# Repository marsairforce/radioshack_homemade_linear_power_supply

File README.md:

# Vintage Adjustable Linear Power Supply

Updating and improving on a very early project I built.

* Partly because I want something to do more things - dual tracking adjustable regulated outputs.
* Partly because I wanted to see how far I have come in my design skills from 10 year old me.
* Partly because I am bored

 I have been wanting to get more into analog circuits, like op-amp circuits and amplifiers. Building these on breadboards has always been challenging for me because I have always had only one bench power supply.  I have a modern bench power supply, but it also only has one output on it.

## TL;DR

This is now a dual channel, double trackking voltage power supply.

Each channel can do about +/-1.2V to +/-20V at about 1A

## Analysis

I created this (I think) when I was in grade 4. So probably around 1987?

* Simple 317 regulator based adjustable power supply.

* Most components were baught from local Radio Shack store in St Vital mall.

  * Radio Shack project box.
  * 18V CT, 2A (36VA?) transformer.
  * Bridge Rectifier.
  * 2200uF capacitor
  * 317 volt regulator on free hanging heatsink.
  * Basic power connector, switch, fuze, with shitty heat shrink tubing on it.
  * Analog DC volt meter.
  * Indicator lamp, but bulb burnt out so I replaced it at some time with a LED stuffed into the lamp holder.
  * A pointless inline fuse holder, with a 2A fuse. This never would blow because the thing can only source 1A
  * Adjustable voltage knob - I remember getting this multi turn potentiometer from Active Electronics.
  * Custom etched single sided PCB
  * Serrible banana plug jacks.
  * Board standoffs (Active Electronics - I still have these) with stove bolts from hardware store.

I would like to say "I have come a long way since then". But at the same time, not really.

* I don't have a convenient way to make circuit boards at home any more.

This gem was hand drawn with a sharpie and then using a liquid tin to protect the copper.

In hindsight this is a terrible board layout.

* I still do not have good nuts and bolts hardware to mount circuit boards.

I have learned or improved a little bit more since I built this:

* I do have much better selection of wires now.

* My soldering skills are a lot better. This thing looks like a Halloween house of horrors.

## Original Schematic

I created this in Kicad

This still functioned very well.

Funny notes as I was taking the old circuit apart.

* The C1 makes no sense. Why did I think I needed to have a ac line capacitor here? I probably had these and copied what I saw in other power supplies.
* The F1 should be after the switch on the hot side.
* The wires from J1, S1, T1 were a white lamp cord. I remember having this and using it for everything.
* The wires from T1 to the circuit board and everywhere else were from an old datacom cable I salvaged from one of my dad's construction sites. I stripped the cable jacket and used the wires for projects.
* I made a PCB using the kit from RadioShack. It is horrible layout and terrible pattern. But I did it with a sharpie and I was 8.
* The J2 was a metal not insulated binding post. As a kid I converted it into an insulated binding post by placing a piece of plastic drinking straw around the metal screw part of the  between the connector and the chassis. Somehow it continued to work all these years.

## Improvements

As usual I can't leave anything alone. Nothing is ever truly completed is it.

I ripped apart the old circuit and removed the parts from the chassis.  The front panel and bottom was a bit bent up from this being knocked around in storage I guess.

### Support more current output

* [Researching](https://www.homemade-circuits.com/lm317-with-outboard-current-boost/) adding a transistor to boost the current handling.

* https://www.ti.com/lit/ds/slvs044x/slvs044x.pdf

This is fun. But I think this is too complicated. And the parts and heatsinks will take up too much space in this small chassis.

And considering the power transformer here is very small, I would be able to fully use this.

Instead, let's just use a [LD1085D2T-R‎](https://www.digikey.ca/product-detail/en/LD1085D2T-R/497-3424-1-ND/669200/?itemSeq=339103460). This has a power capacity of 3A.  And being a surface mount device I can use the PCB as the heatsink.

## More voltage outputs

I think having a single output is kind of useless for me.

* To build a variable output. But to build it as a [dual tracking control](https://www.youtube.com/watch?v=AOIxS7iOxbU). This is pretty neat. But the devil in the details of the op-amp needs a +/- power supply.

* A +/-15V supply for op-amps.

> HEY!!  I had "build a nice bench top op-amp power supply as one of my active projects.  I never got it out of design phase though. But what if I just build it into this existing power supply chassis I alredy have.  That seems practical to me too.

The dual tracking adjustable supply is neat as I do not have this with my existing bench top power supplies.

I think it is going to be challenging to fit all this stuff into this small chassis.

I compromised and designed a dual output dual tracking power supply. This gives me two channels of adjustable +/- voltage.

Each channel allows the use of a trimmer pot on the pcb, so it can practically behave as a fixed voltage.

I think I will go with having one channel be variable from the front panel and the other to be set with a trimmer.

## Updated schematic

This is in the updated folder, opamp_power_supply sub folder.

I started off with this Hammoond 229B34. It is a nice 12VA low profile transformer. It is semi-toroidial, so it has ok magnetic shielding as well. I was looking for something that had low electrical and magnetic noise. The original idea was to create a power supply suitable for powering audio op-amp circuits.

The configuration of this transformer lends itself to being able to use the secondary in series or in parallel.  In this case the secondary series voltage was about 38V. I don't need a power supply to go that high, so most of the voltage would be disapated as heat.
using the transformer secondary in parallel gives about 18V and about 600ma current output. But then is only single supply.
The approach here where I use them as separate secondaries is somewhere in between. I have an ok voltage to supply the regulators and a bit more or basically the same current than if i used the secondary in series.  I just need to use more diodes.  Fortunately diodes are cheap.

I chose to use Shotkey diodes here instead of regular rectifier diodes, because they have a lower forward voltage drop. Which means less energy gets lost as heat. These looke like they were diode arrays for use in the secondary of a switch mode power supply. Where you would want two dioded connected together, as for a full wave rectifier with the center tap right. But here I just use them in parallel. Because it helps further with the forward voltage losses. And I have them in the package for free. I could get a single diode in a DPAK pacakge. But these were pretty cheap as well.

I wanted rediculous large filter capacitors. There are some formulas I keep finding to calculate the capacitor size for the ripple voltage under an expected load. So I tried to use those. But then when you use regulators these all go askew anyway. The regulators specify they need a minimum of a relatively small capacitance. So these are going to be more than enough anyway. Again, wanting to have the perfect smooth DC supply for use in audio quality op-amp circuits.

Each channel a pair of regulators. These are the 317 and 337 adjustable family of regulators.

And then the op-amp there to provide the inverted voltage reference to the negative regulator. This allows for a single control voltage from one adjustable resistor to have both regulators adjust at the same time.

And then more filtering after the regulation. I have ceramic and electrolytic capacitors to help with transients.

Of course the devil is in the details.

This op-amp requires its own +/-15V power supply.  But we are already building a power supply. And these are adjustable outputs at that.

So I added a small current +/-15V regulators here. These are smlal so-8 packages that are good for up to about 100mA. The op-amps I have here use much less than that.  I do not expose this supply as an output to be used off the power supply. Though I guess I could have. I didn't want this internal power that is used to control the regulators to be compromised by loading or shorting it out.

## PCB

I ordered the PCB from

<a href="https://oshpark.com/shared_projects/tLXbXLEt"></img></a>

It arrived a few weeks later.

I had the parts all ready to go. I ordered enough to build 3 modules. Because I pay for and get 3 boards anyway!. Sometimes that is a nuissance. But sometimes you can use it as a feature like this I guess.

I plan to build one into this power supply, to build a stand-alone op-amp power supply in a box. Where I set the outputs to +/-15V and +/-12V. And to have another one for use in a tube amplifier project idea I am still designing.

## Assembly

I built all three boards at the same time. At each step where I could I did some testing to make sure it was working.

* The transformer, fuze, and input connector, rectifier diodes - able to see rectified DC ripples on the filter capacitor pads.
* The capacitors - able to see DC voltage
* The 15V regulators - able to measure +/-15V
* The capacitors and resistors - bulk components. Test for continuity.
* The regulators - measure and test adjusting the voltage.

Put the board on some standoffs and mount it into the chassis

I didn't think about the potentiometers. I was just going to use the one I had from before. But when I was putting the new power supply PCB into the case I discovered it is not working very well. It feels all loose. I probably dropped this at some time and broke it. It still works but is very jittery when you turn it.

Time to replace this.

Since I am replacing it anyway and I do have space to add another potentiometer for the second channel I might as well do that now.

And get some nice knobs for this. I am tired of the classic single knob I have had forever.

I will need some more output connectors on the back. Drill in some new holes and mount the connectors.

And then wire up the connectors to the screw terminals on the PCB.

Hook up the meter.

I only bother tracking the positive voltage, since the negative will track what ever the positive is but be opposite polarity right.

I added a toggle switch beside the meter so I can switch which channel is currently being displayed on the meter.

Fix the indicator LED and put it back together.

A little bit of label maker ties it all together.

Ready to roll.

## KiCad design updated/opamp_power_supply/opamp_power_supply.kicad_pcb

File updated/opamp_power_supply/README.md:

# A dual rail power supply for use in op-amp circuits

It keeps coming up where I need to get a good dual rail op-amp power supply in projects.

Wanting to design a power supply module that is economical and small form factor and general purpose enough to be put into various applications as needed.

## Requirements

* Input from 120VAC
* IEC power connector, fuze. Optional switch.
* +15V and -15V outputs. Perhaps up to 1A is all we would need.
* A +5V output for other logic circuits in the project.

## Nice to have

* Efficient. Not using linear regulators. It would be quite readily available to use a transformer, a 7815, 7915 regulators, capacitors. But transformers tend to be expensive.
* Small. Not using large bulky and expensive transformer.
* Low noise. Suitable for use in audio applications.

## Investigation

It turns out What I am looking for just exists as a module: https://www.digikey.ca/product-detail/en/xp-power/ECL15UT03-E/1470-1185-ND/4487566 $80

Done.

No project to do at this time.

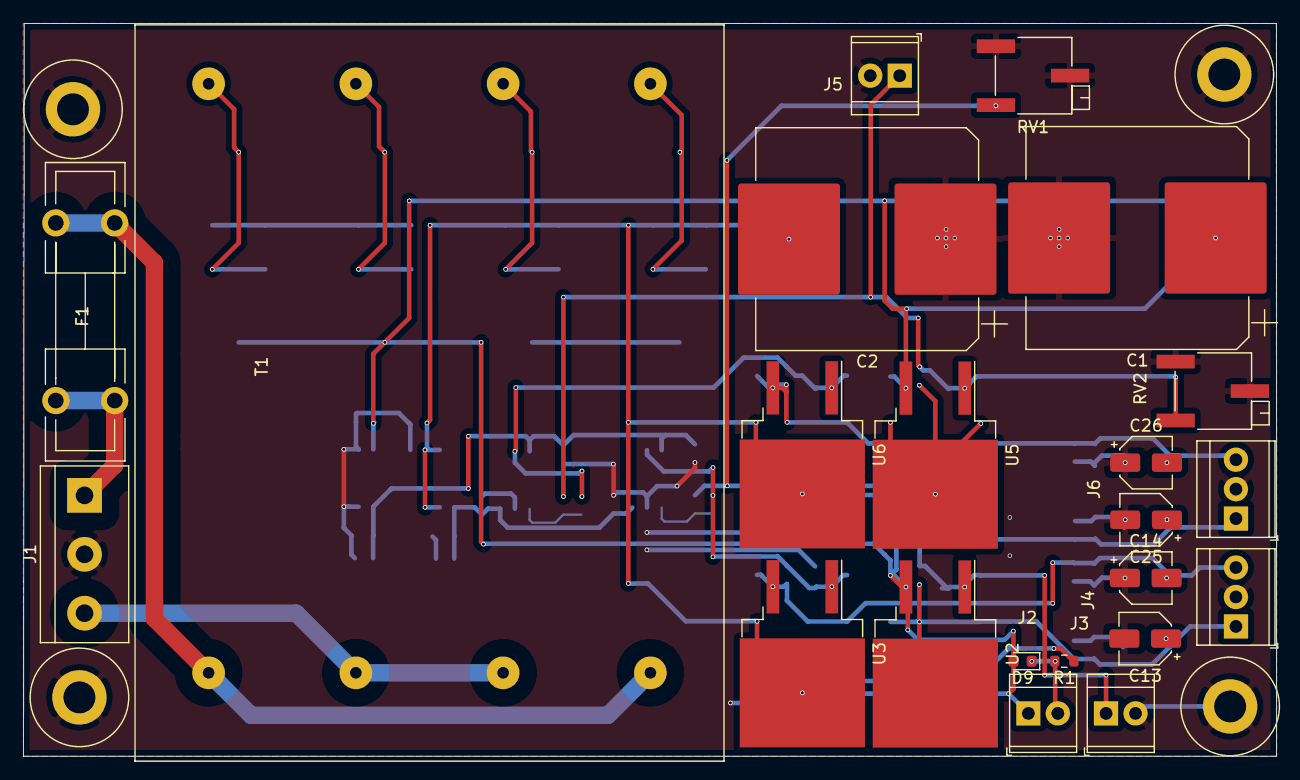
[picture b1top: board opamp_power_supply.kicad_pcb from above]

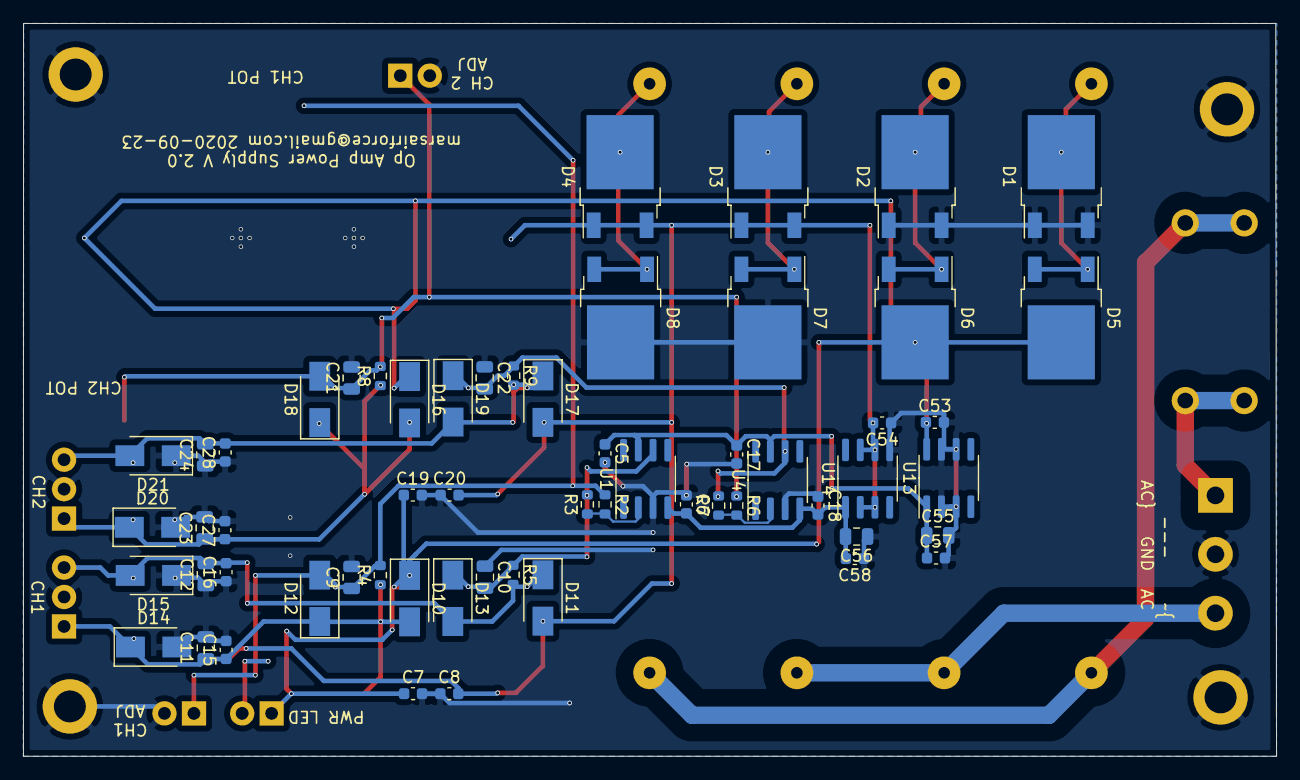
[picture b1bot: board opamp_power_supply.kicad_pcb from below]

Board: 2 copper layers, 108.1 x 63.2 mm, 84 parts (58 on the bottom side), 23 nets.

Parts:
C1, C2: 3000uF; CP_Elec_18x22
C5, C6, C7, C8, C15, C16, C17, C18, C19, C20, C27, C28, C53, C54, C57, C58: 0.1uF; C_0603_1608Metric
C9, C10, C11, C12, C21, C22, C23, C24, C55, C56: 10uF; C_0805_2012Metric
C13, C14, C25, C26: 10uF; CP_Elec_4x5.8
D1, D2, D3, D4, D5, D6, D7, D8: MBRD6100CTTR; TO-252-2
D9: LED; D_0603_1608Metric
D10, D11, D12, D13, D14, D15, D16, D17, D18, D19, D20, D21: S1M-13-F; D_SMA
F1: 120mA; Fuseholder5x20_horiz_open_lateral_Type-II
H1, H2, H3, H4: hole; Mounting_Hole_Plated_M2.5
J1: AC IN; TerminalBlock-3_P5.08mm
J2: power led; TerminalBlock_1x02_P2.54mm_Horizontal
J3, J5: adj; TerminalBlock_1x02_P2.54mm_Horizontal
J4, J6: +/-out; TerminalBlock_1x03_P2.54mm_Horizontal
R1: 1.5K; R_0603_1608Metric
R2, R3, R6, R7: 10K; R_0603_1608Metric
R4, R5, R8, R9: 240; R_0603_1608Metric
RV1, RV2: 5K; Potentiometer_Bourns_3269P_Horizontal
T1: Hammond_229B34; Hammond_229_series_low_profile_transformers
U1, U4: TL071; SOIC-8_3.9x4.9mm_P1.27mm
U2, U5: LD1085; TO-263-2
U3, U6: LM337_TO263; TO-263-2
U13: L78L15_SO8; SOIC-8_3.9x4.9mm_P1.27mm
U14: L79L15_SO8; SOIC-8_3.9x4.9mm_P1.27mm

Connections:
/REG1/V_NEG: C2.2, C8.2, C20.2, C54.2, D3.1, D3.3, D4.1, D4.3, D11.2, D17.2, R1.1, U3.2, U6.2, U14.2, U14.3, U14.6, U14.7
/REG1/V_POS: C1.1, C7.1, C19.1, C53.1, D5.2, D6.2, D9.2, D10.1, D16.1, J2.1, U2.3, U5.3, U13.8
/REG1/vb+: C5.1, C17.1, C55.1, C57.1, U1.7, U4.7, U13.1
/REG1/vb-: C6.2, C18.2, C56.2, C58.2, U1.4, U4.4, U14.1
Earth: C1.2, C2.1, C5.2, C6.1, C7.2, C8.1, C9.2, C10.1, C11.2, C12.1, C13.2, C14.1, C15.2, C16.1, C17.2, C18.1, C19.2, C20.1, C21.2, C22.1, C23.2, C24.1, C25.2, C26.1, C27.2, C28.1, C53.2, C54.1, C55.2, C56.1, C57.2, C58.1, D1.1, D1.3, D2.1, D2.3, D7.2, D8.2, D14.2, D15.1, D20.2, D21.1, H1.1, H2.1, H3.1, H4.1, J1.2, J3.2, J4.2, J5.2, J6.2, RV1.2, RV1.3, RV2.2, RV2.3, U1.3, U4.3, U13.2, U13.3, U13.6, U13.7, U14.5
unnamed: C9.1, D12.2, J3.1, R2.1, R4.2, RV1.1, U2.1
unnamed: C10.2, D13.1, R3.2, R5.1, U1.6, U3.1
unnamed: C11.1, C13.1, C15.1, D10.2, D12.1, D14.1, J4.1, R4.1, U2.2
unnamed: C12.2, C14.2, C16.2, D11.1, D13.2, D15.2, J4.3, R5.2, U3.3
unnamed: C21.1, D18.2, J5.1, R6.1, R8.2, RV2.1, U5.1
unnamed: C22.2, D19.1, R7.2, R9.1, U4.6, U6.1
unnamed: C23.1, C25.1, C27.1, D16.2, D18.1, D20.1, J6.1, R8.1, U5.2
unnamed: C24.2, C26.2, C28.2, D17.1, D19.2, D21.2, J6.3, R9.2, U6.3
unnamed: D1.2, D5.1, D5.3, T1.7
unnamed: D2.2, D6.1, D6.3, T1.8
unnamed: D3.2, D7.1, D7.3, T1.6
unnamed: D4.2, D8.1, D8.3, T1.5
unnamed: D9.1, J2.2, R1.2
unnamed: F1.1, T1.1, T1.3
unnamed: F1.2, J1.1
unnamed: J1.3, T1.2, T1.4
unnamed: R2.2, R3.1, U1.2
unnamed: R6.2, R7.1, U4.2

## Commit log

2020-09-26 add updated text
2020-10-15 update with pictures after rebuilding
2020-10-15 rotate picture
